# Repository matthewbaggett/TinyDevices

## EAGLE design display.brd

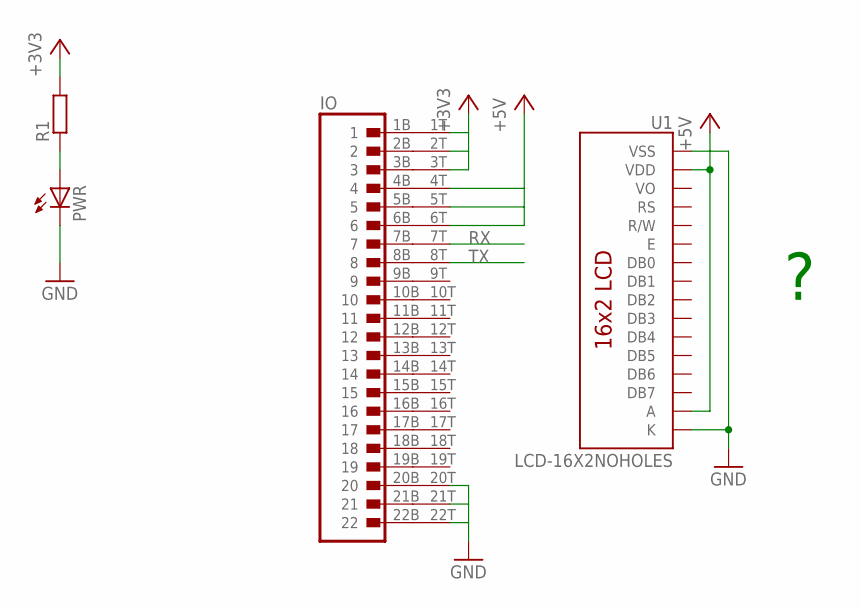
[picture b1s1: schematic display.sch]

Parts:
IO: SIMBRD22
PWR: LED1206; LED-1206
R1: R-EU_R0805; R0805
U1: LCD-16X2NOHOLES; LCD-16X2_NOHOLES

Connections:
+3V3: IO.1T (A1), IO.2T (A2), IO.3T (A3), R1.2
+5V: IO.4T (A4), IO.5T (A5), IO.6T (A6), U1.2 (VDD), U1.15 (A)
GND: IO.20T (A20), IO.21T (A21), IO.22T (A22), PWR.C, U1.1 (VSS), U1.16 (K)
unnamed: PWR.A, R1.1
RX: IO.7T (A7)
TX: IO.8T (A8)

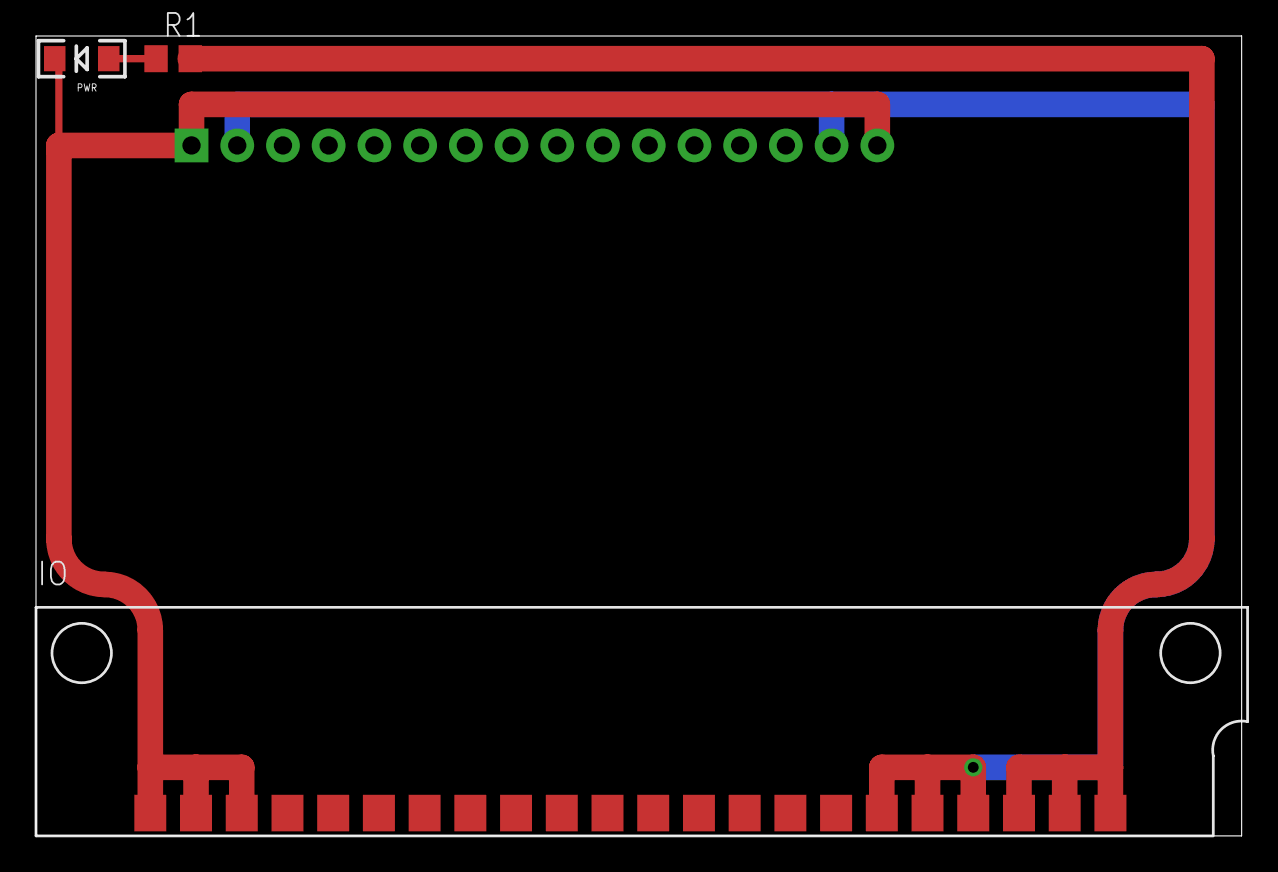
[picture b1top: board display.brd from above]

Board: 2 copper layers, 67.0 x 44.4 mm, 4 parts (0 on the bottom side), 4 nets.

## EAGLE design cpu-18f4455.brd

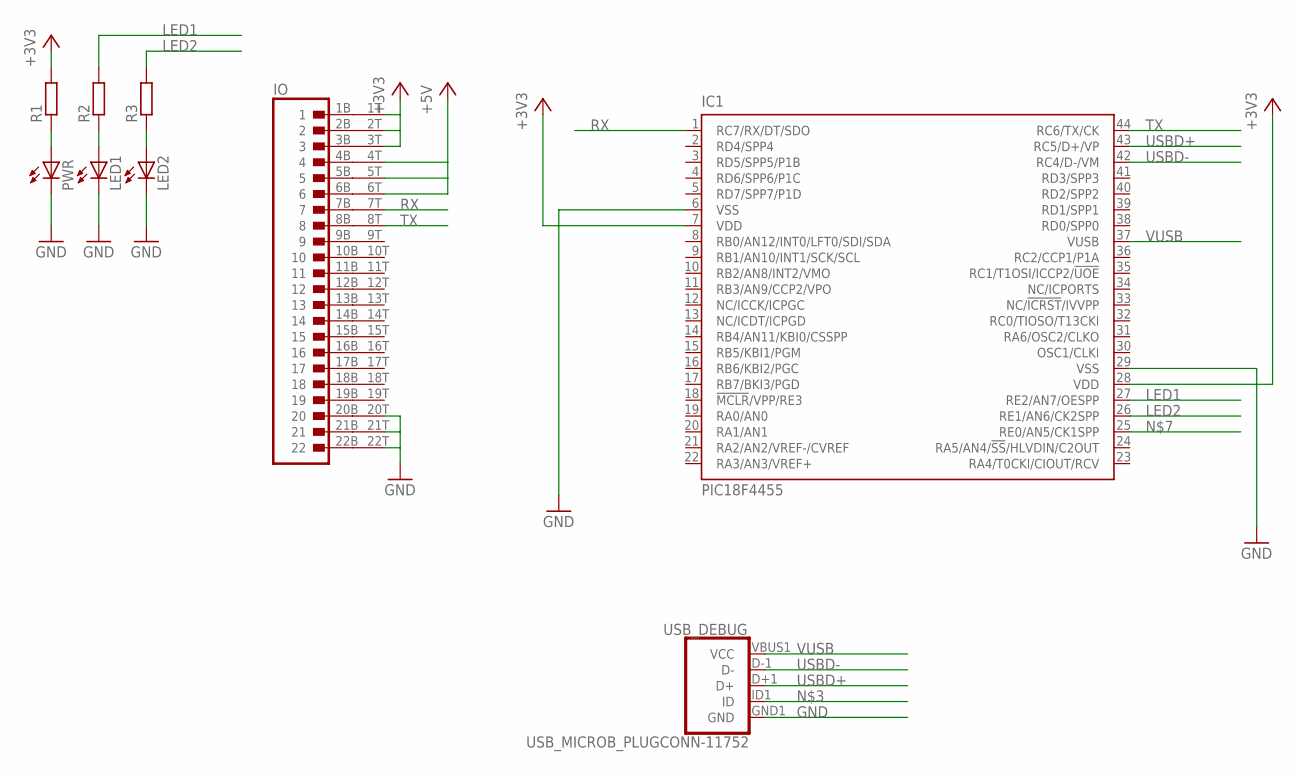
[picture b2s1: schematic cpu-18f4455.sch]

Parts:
IC1: PIC18F4455; TQFP44
IO: SIMBRD22
LED1, LED2: LED1206; LED-1206
PWR: LED1206; LED-1206
R1, R2, R3: R-EU_R0805; R0805
USB_DEBUG: USB_MICROB_PLUGCONN-11752; USB-B-MICRO-SMD_V03

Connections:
+3V3: IC1.7 (VDD), IC1.28 (VDD), IO.1T (A1), IO.2T (A2), IO.3T (A3), R1.2
+5V: IO.4T (A4), IO.5T (A5), IO.6T (A6)
GND: IC1.6 (VSS), IC1.29 (VSS), IO.20T (A20), IO.21T (A21), IO.22T (A22), LED1.C, LED2.C, PWR.C, USB_DEBUG.GND1 (GND)
LED1: IC1.27 (RE2/AN7/OESPP), R2.2
LED2: IC1.26 (RE1/AN6/CK2SPP), R3.2
unnamed: PWR.A, R1.1
unnamed: LED1.A, R2.1
unnamed: LED2.A, R3.1
RX: IC1.1 (RC7/RX/DT/SDO), IO.7T (A7)
TX: IC1.44 (RC6/TX/CK), IO.8T (A8)
USBD+: IC1.43 (RC5/D+/VP), USB_DEBUG.D+1 (D+)
USBD-: IC1.42 (RC4/D-/VM), USB_DEBUG.D-1 (D-)
VUSB: IC1.37 (VUSB), USB_DEBUG.VBUS1 (VCC)

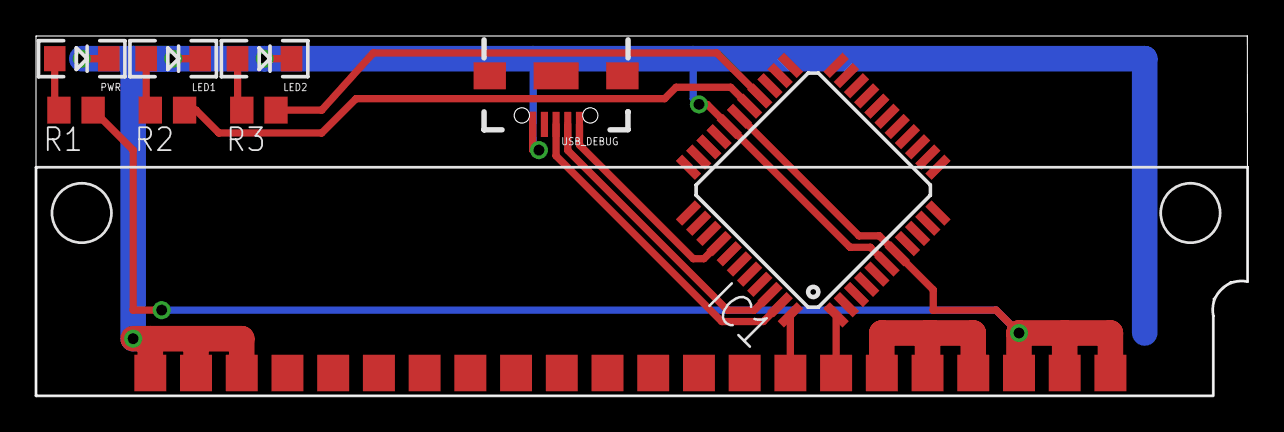
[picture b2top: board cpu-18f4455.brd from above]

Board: 2 copper layers, 67.3 x 20.0 mm, 9 parts (0 on the bottom side), 13 nets.

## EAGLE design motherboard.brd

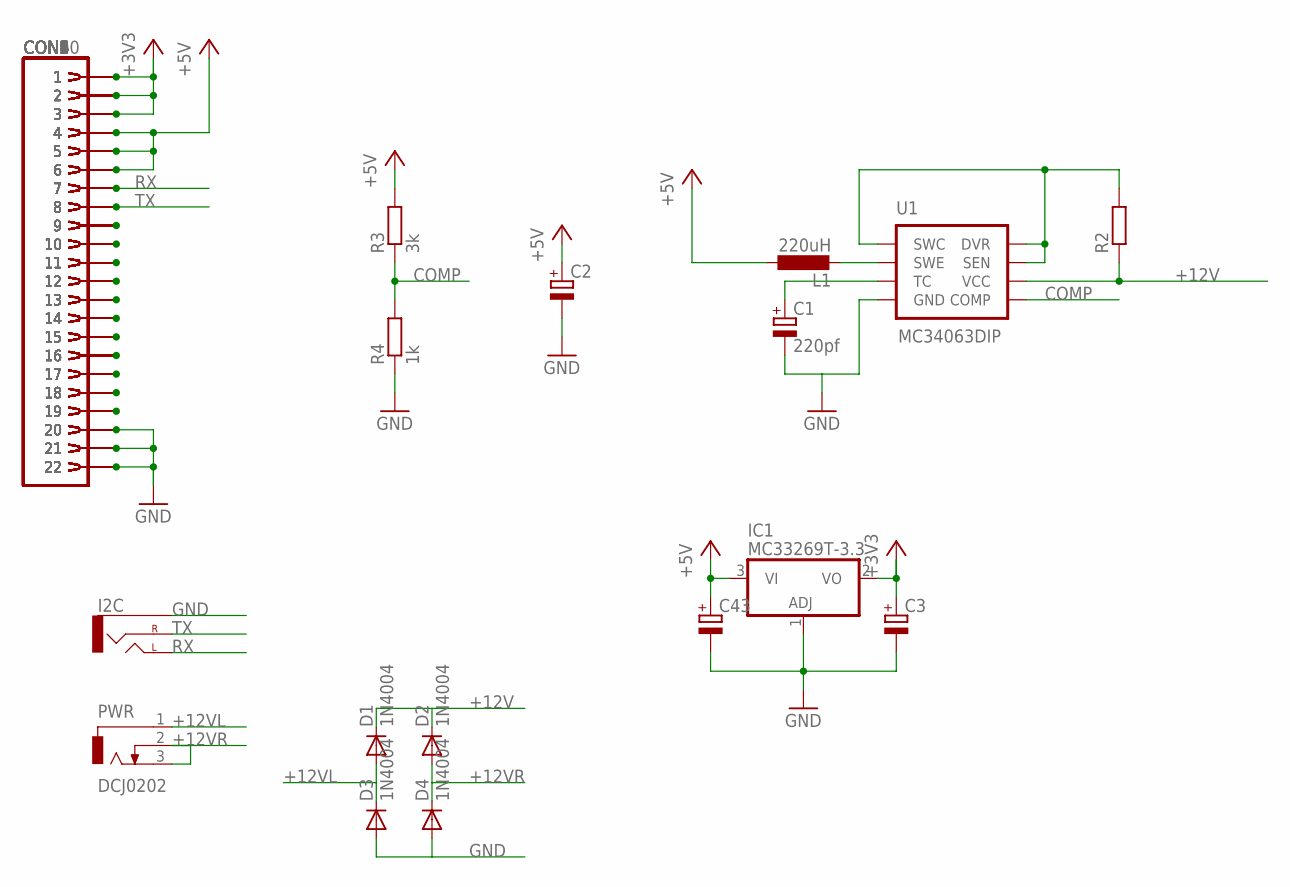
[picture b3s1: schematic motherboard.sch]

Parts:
C1: 220pf; E3,5-8
C2: CPOL-EUE3.5-8; E3,5-8
C3, C43: CPOL-EUE2-4; E2-4
CON1, CON2, CON3, CON4, CON5, CON6, CON7, CON8, CON9, CON10: SIMM22
D1, D2, D3, D4: 1N4004; DO41-10
I2C: AUDIO-JACKPTH; AUDIO-JACK
IC1: MC33269T-3.3; TO220V
L1: 220uH; 0204/7
PWR: DCJ0202
R2: R-EU_0204/7; 0204/7
R3: 3k; 0204/7
R4: 1k; 0204/7
U1: MC34063DIP; DIP-08

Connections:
+3V3: C3.+, CON1.1, CON1.2, CON1.3, CON2.1, CON2.2, CON2.3, CON3.1, CON3.2, CON3.3, CON4.1, CON4.2, CON4.3, CON5.1, CON5.2, CON5.3, CON6.1, CON6.2, CON6.3, CON7.1, CON7.2, CON7.3, CON8.1, CON8.2, CON8.3, CON9.1, CON9.2, CON9.3, CON10.1, CON10.2, CON10.3, IC1.2 (VO)
+5V: C2.+, C43.+, CON1.4, CON1.5, CON1.6, CON2.4, CON2.5, CON2.6, CON3.4, CON3.5, CON3.6, CON4.4, CON4.5, CON4.6, CON5.4, CON5.5, CON5.6, CON6.4, CON6.5, CON6.6, CON7.4, CON7.5, CON7.6, CON8.4, CON8.5, CON8.6, CON9.4, CON9.5, CON9.6, CON10.4, CON10.5, CON10.6, IC1.3 (VI), L1.1, R3.2
+12V: D1.C, D2.C, R2.1, U1.6 (VCC)
+12VL: D1.A, D3.C, PWR.1
+12VR: D2.A, D4.C, PWR.2, PWR.3
COMP: R3.1, R4.2, U1.5 (COMP)
GND: C1.-, C2.-, C3.-, C43.-, CON1.20, CON1.21, CON1.22, CON2.20, CON2.21, CON2.22, CON3.20, CON3.21, CON3.22, CON4.20, CON4.21, CON4.22, CON5.20, CON5.21, CON5.22, CON6.20, CON6.21, CON6.22, CON7.20, CON7.21, CON7.22, CON8.20, CON8.21, CON8.22, CON9.20, CON9.21, CON9.22, CON10.20, CON10.21, CON10.22, D3.A, D4.A, I2C.SLEEVE, IC1.1 (ADJ), R4.1, U1.4 (GND)
unnamed: L1.2, U1.2 (SWE)
unnamed: R2.2, U1.1 (SWC), U1.7 (SEN), U1.8 (DVR)
unnamed: C1.+, U1.3 (TC)
unnamed: CON1.19, CON2.19, CON3.19, CON4.19, CON5.19, CON6.19, CON7.19, CON8.19, CON9.19, CON10.19
unnamed: CON1.18, CON2.18, CON3.18, CON4.18, CON5.18, CON6.18, CON7.18, CON8.18, CON9.18, CON10.18
unnamed: CON1.17, CON2.17, CON3.17, CON4.17, CON5.17, CON6.17, CON7.17, CON8.17, CON9.17, CON10.17
unnamed: CON1.16, CON2.16, CON3.16, CON4.16, CON5.16, CON6.16, CON7.16, CON8.16, CON9.16, CON10.16
unnamed: CON1.15, CON2.15, CON3.15, CON4.15, CON5.15, CON6.15, CON7.15, CON8.15, CON9.15, CON10.15
unnamed: CON1.14, CON2.14, CON3.14, CON4.14, CON5.14, CON6.14, CON7.14, CON8.14, CON9.14, CON10.14
unnamed: CON1.13, CON2.13, CON3.13, CON4.13, CON5.13, CON6.13, CON7.13, CON8.13, CON9.13, CON10.13
unnamed: CON1.12, CON2.12, CON3.12, CON4.12, CON5.12, CON6.12, CON7.12, CON8.12, CON9.12, CON10.12
unnamed: CON1.11, CON2.11, CON3.11, CON4.11, CON5.11, CON6.11, CON7.11, CON8.11, CON9.11, CON10.11
unnamed: CON1.10, CON2.10, CON3.10, CON4.10, CON5.10, CON6.10, CON7.10, CON8.10, CON9.10, CON10.10
unnamed: CON1.9, CON2.9, CON3.9, CON4.9, CON5.9, CON6.9, CON7.9, CON8.9, CON9.9, CON10.9
RX: CON1.7, CON2.7, CON3.7, CON4.7, CON5.7, CON6.7, CON7.7, CON8.7, CON9.7, CON10.7, I2C.TIP (LEFT)
TX: CON1.8, CON2.8, CON3.8, CON4.8, CON5.8, CON6.8, CON7.8, CON8.8, CON9.8, CON10.8, I2C.RING (RIGHT)

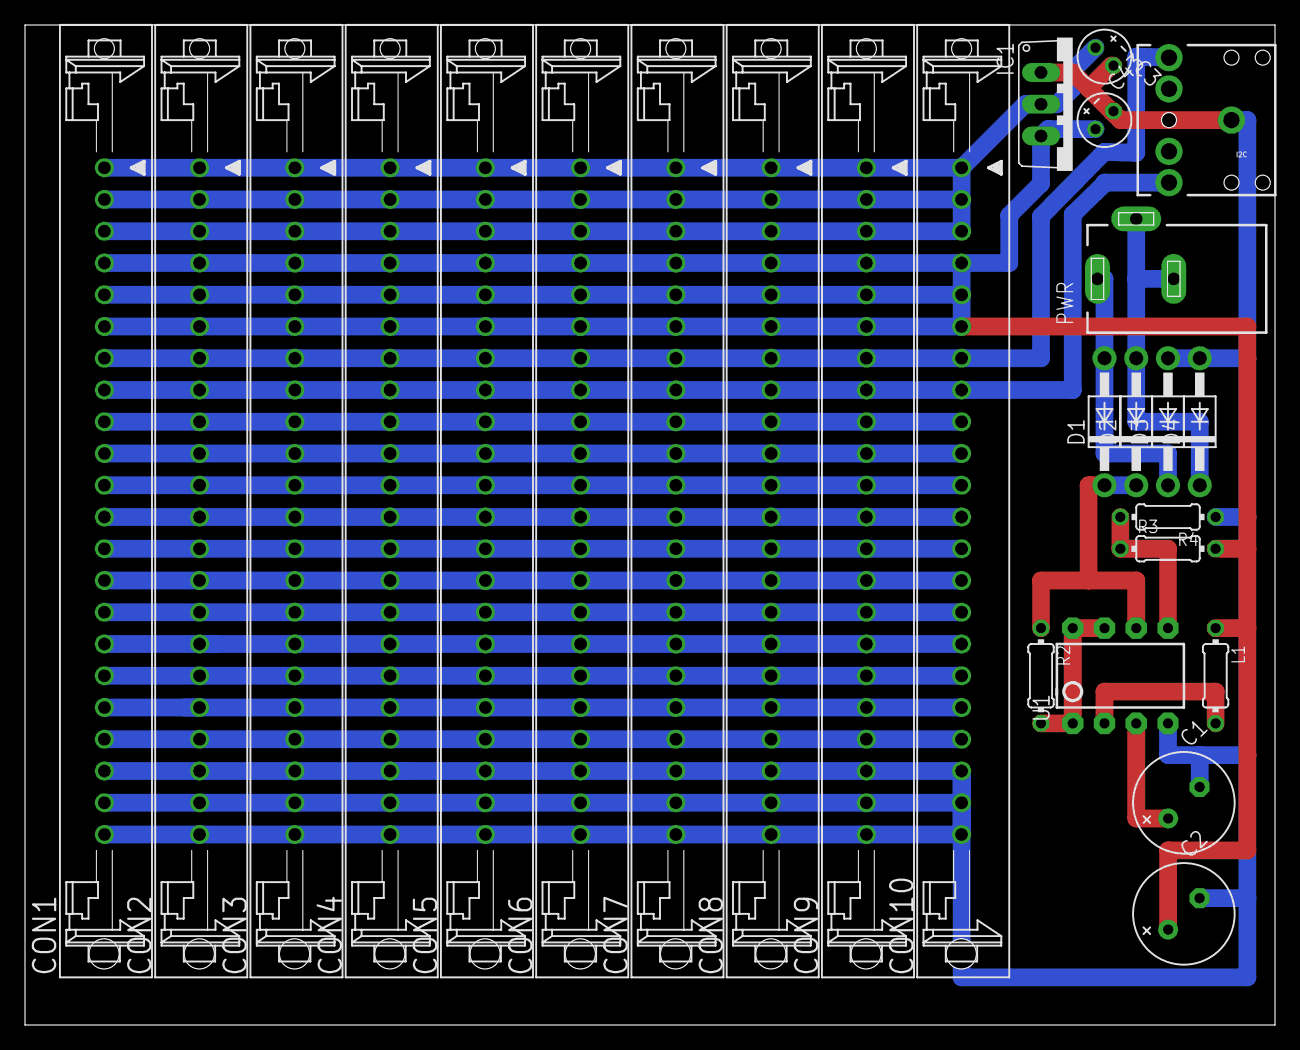
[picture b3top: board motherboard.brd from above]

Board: 2 copper layers, 100.0 x 80.0 mm, 26 parts (0 on the bottom side), 23 nets.

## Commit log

2014-04-03 Added 3.3v regulator and circuit
2014-04-03 I wired power backwards. I am the dumb. ._.;
2014-04-03 Half-completed display.. thing.
2014-04-03 Project updated

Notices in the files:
parts and their libraries:
SparkFun-LED: Licensing: Creative Commons ShareAlike 4.0 International - https://creativecommons.org/licenses/by-sa/4.0
